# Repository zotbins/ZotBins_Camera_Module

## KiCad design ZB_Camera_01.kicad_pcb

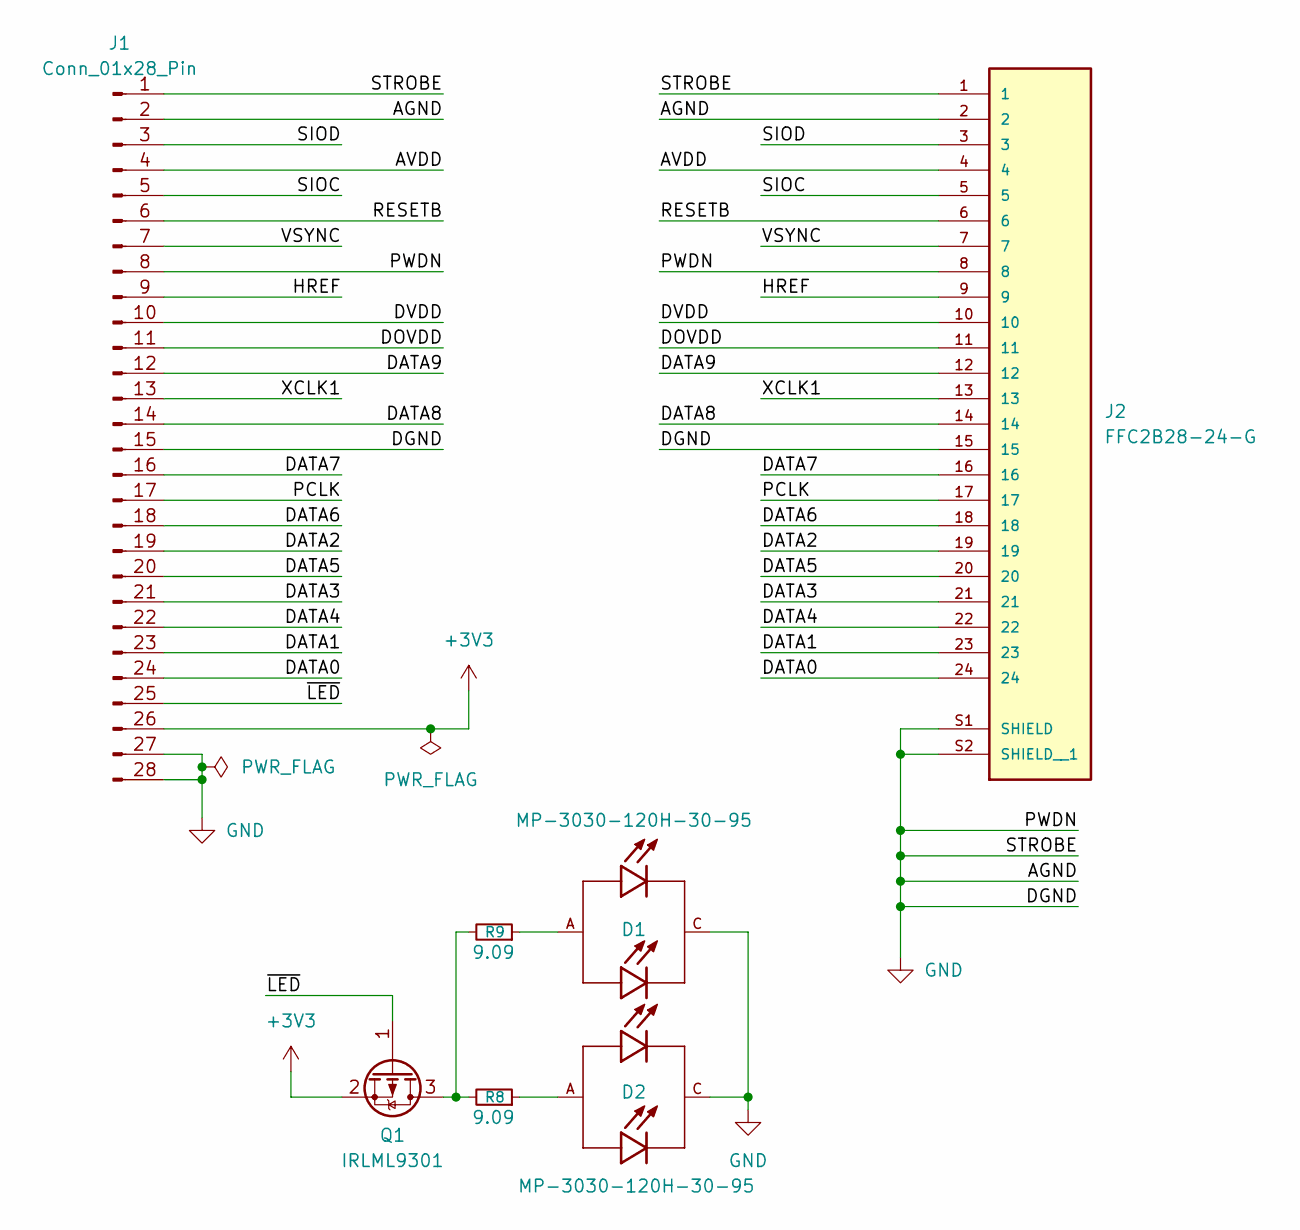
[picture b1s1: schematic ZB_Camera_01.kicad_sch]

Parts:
D1, D2: MP-3030-120H-30-95; LED_MP-3030-120H-30-95; PARTREV Rev 03
J1: Conn_01x28_Pin; TE_2-84953-8_1x28-1MP_P1.0mm_Horizontal
J2: FFC2B28-24-G; GCT_FFC2B28-24-G; PARTREV A
Q1: IRLML9301; SOT-23
R8, R9: 9.09; R_Axial_DIN0207_L6.3mm_D2.5mm_P10.16mm_Horizontal

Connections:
+3V3: J1.26, Q1.2 (S)
/AVDD: J1.4, J2.4
/DATA0: J1.24, J2.24
/DATA1: J1.23, J2.23
/DATA2: J1.19, J2.19
/DATA3: J1.21, J2.21
/DATA4: J1.22, J2.22
/DATA5: J1.20, J2.20
/DATA6: J1.18, J2.18
/DATA7: J1.16, J2.16
/DATA8: J1.14, J2.14
/DATA9: J1.12, J2.12
/DOVDD: J1.11, J2.11
/DVDD: J1.10, J2.10
/HREF: J1.9, J2.9
/PCLK: J1.17, J2.17
/RESETB: J1.6, J2.6
/SIOC: J1.5, J2.5
/SIOD: J1.3, J2.3
/VSYNC: J1.7, J2.7
/XCLK1: J1.13, J2.13
/~LED: J1.25, Q1.1 (G)
GND: D1.C, D2.C, J1.1, J1.2, J1.8, J1.15, J1.27, J1.28, J2.1, J2.2, J2.8, J2.15, J2.S1 (SHIELD), J2.S2 (SHIELD__1)
unnamed: D1.A, R9.1
unnamed: D2.A, R8.1
unnamed: Q1.3 (D), R8.2, R9.2

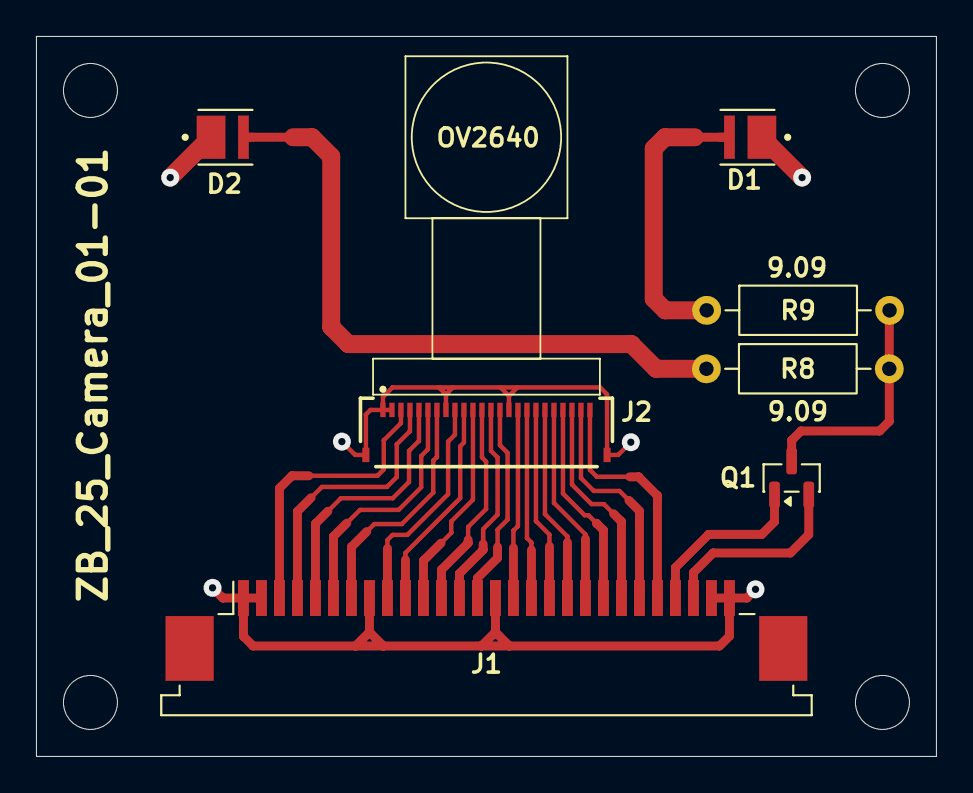
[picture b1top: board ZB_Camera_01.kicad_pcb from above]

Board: 2 copper layers, 50.0 x 40.0 mm, 7 parts (0 on the bottom side), 26 nets.

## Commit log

2025-11-13 iteration_1
2025-11-13 Add initial content to README.md
2025-11-14 added dimension indicators
2025-11-18 ordered version + gerber
